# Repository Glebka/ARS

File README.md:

# ARS - Alarm System

My first project based on the STM32 microcontroller family. It consists of an alarm module and a receiver. The alarm module utilizes the RCWL-0516 motion sensor, the STM32F030K6T6 microcontroller, which wakes up upon interruption from the sensor, and communicates the alarm using the LoRa module RA-02 at 433 MHz.

As the receiver, an ESP32 TTGO LoRa 433MHz development board with an OLED display is used. The receiver spends most of its time in a sleeping state to reduce power consumption. Upon receiving an alarm signal, the receiver wakes up, displays a text status on the screen, and activates an LED indicator. The LED continues to blink even in sleep mode until the user resets the alarm state. This is made possible by the ULP coprocessor.

## TODO

- Configure the alarm module to operate on battery power.
- Implement a buzzer on the receiver to provide an audible signal in case of an alarm.
- Redesign the enclosure for the receiver.
- Design an enclosure for the alarm module.
- Add encryption
- Add protection from replay attacks

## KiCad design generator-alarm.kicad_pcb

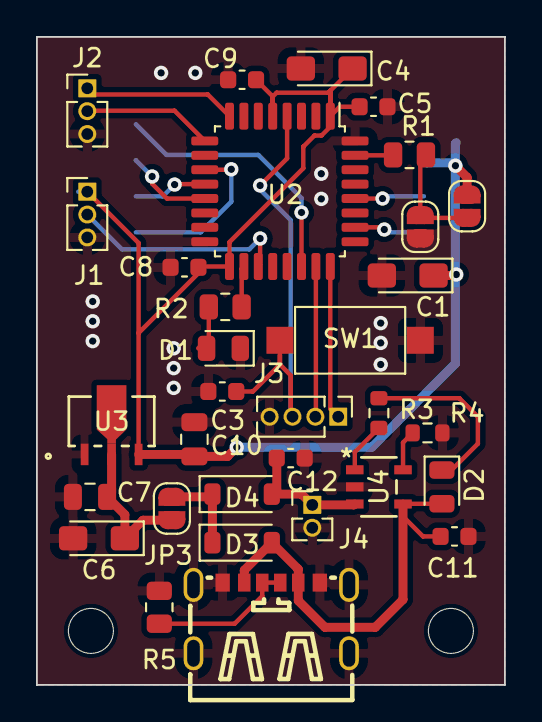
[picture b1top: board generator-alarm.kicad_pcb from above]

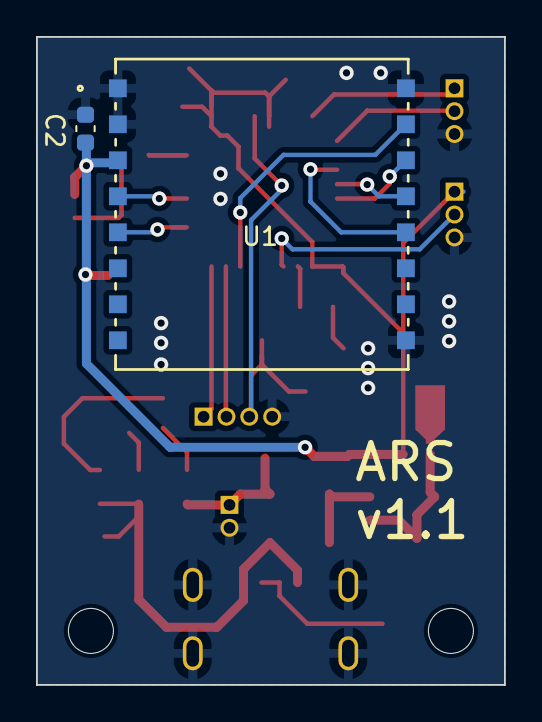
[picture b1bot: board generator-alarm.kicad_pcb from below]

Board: 2 copper layers, 26.0 x 36.0 mm, 36 parts (2 on the bottom side), 26 nets.

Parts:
C1, C4, C6: 10u; CP_EIA-3216-10_Kemet-I_Pad1.58x1.35mm_HandSolder
C2, C3, C5, C8, C9: 0.1u; C_0603_1608Metric
C7, C10: 1u; C_0805_2012Metric
C11: 1u; C_0603_1608Metric
C12: 10u; C_0603_1608Metric
D1: LED; LED_0805_2012Metric
D2: LED-Blue; LED_0805_2012Metric
D3, D4: MBR0520LT1; D_SOD-123
H1, H2: MountingHole; MountingHole_2.5mm
J1: Sensor; PinHeader_1x03_P1.27mm_Vertical
J2: UART; PinHeader_1x03_P1.27mm_Vertical
J3: SWD; PinHeader_1x04_P1.27mm_Vertical
J4: BAT; PinHeader_1x02_P1.27mm_Vertical
JP1, JP2, JP3: SolderJumper_2_Open; SolderJumper-2_P1.3mm_Open_RoundedPad1.0x1.5mm
R1: 10k; R_0805_2012Metric
R2: 1k; R_0805_2012Metric
R3: 3k; R_0603_1608Metric
R4: 5k; R_0603_1608Metric
R5: 5.1k; R_0805_2012Metric
SW1: RESET; SW_SPST_CK_RS282G05A3
U1: RA-02; RA-02_AIT
U2: STM32F030K6Tx; LQFP-32_7x7mm_P0.8mm
U3: XC6206P332PR-G; SOT-89_TOR
U4: TP4065-4.2V-SOT25-R; SOT-23-5L_TPW
USB1: TYPE-C_6P; TYPE-C-SMD_TYPE-C-6P

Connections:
BAT+: C12.1, D4.2 (A), J4.1, U4.3 (BAT)
BAT-: C1.2, C2.1, C3.1, C4.2, C5.1, C6.2, C7.2, C8.2, C9.2, C10.2, C11.2, C12.2, D1.1 (K), J1.3, J2.3, J3.4, J4.2, JP1.1 (A), R4.2, R5.2, SW1.2, U1.1 (GND), U1.2 (GND), U1.9 (GND), U1.16 (GND), U2.16 (VSS), U2.32 (VSS), U3.1 (VSS), U4.2 (GND), USB1.7 (EH), USB1.A12 (GND), USB1.B12 (GND)
MISO: U1.13 (MISO), U2.12 (PA6)
MOSI: U1.14 (MOSI), U2.13 (PA7)
MOTION_INT: J1.2, U2.19 (PA9)
NRST: C3.2, J3.3, SW1.1, U2.4 (NRST)
unnamed: D1.2 (A), R2.2
unnamed: C11.1, D2.2 (A), D3.2 (A), U4.4 (VCC), USB1.A9 (VBUS), USB1.B9 (VBUS)
unnamed: D2.1 (K), R3.2
unnamed: D3.1 (K), D4.1 (K), JP3.2 (B)
unnamed: JP1.2 (B), JP2.2 (B), R1.1
unnamed: R1.2, U2.31 (BOOT0)
unnamed: R2.1, U2.18 (PA8)
unnamed: R3.1, U4.1 (CHRG)
unnamed: R4.1, U4.5 (PROG)
unnamed: R5.1, USB1.A5 (CC1), USB1.B5 (CC2)
RA_DIO: U1.5 (DIO0), U2.26 (PB3)
RA_NSS: U1.15 (NSS), U2.22 (PA12)
RA_RST: U1.4 (RESET), U2.28 (PB5)
SCK: U1.12 (SCK), U2.11 (PA5)
SWCLK: J3.1, U2.24 (PA14)
SWDIO: J3.2, U2.23 (PA13)
UART_RX: J2.2, U2.9 (PA3)
UART_TX: J2.1, U2.8 (PA2)
V+: C6.1, C7.1, JP3.1 (A), U3.2 (VIN)
VDD: C1.1, C2.2, C4.1, C5.2, C8.1, C9.1, C10.1, J1.1, JP2.1 (A), U1.3 (3.3V), U2.1 (VDD), U2.5 (VDDA), U2.17 (VDD), U3.3 (VOUT)

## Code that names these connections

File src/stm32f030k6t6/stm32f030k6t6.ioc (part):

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Mcu.Name=STM32F030K6Tx
Mcu.Package=LQFP32
Mcu.UserName=STM32F030K6Tx
PA0.Signal=GPIO_Output
PA1.Signal=GPIO_Output
PA10.Signal=GPIO_Output
PA11.GPIOParameters=GPIO_Speed
PA11.GPIO_Speed=GPIO_SPEED_FREQ_LOW
PA11.Signal=GPIO_Output
PA12.GPIOParameters=GPIO_Speed,PinState,GPIO_Label
PA12.GPIO_Label=RA_NSS
PA12.GPIO_Speed=GPIO_SPEED_FREQ_HIGH
PA12.PinState=GPIO_PIN_SET
PA12.Signal=GPIO_Output
PA13.Mode=Serial_Wire
PA13.Signal=SYS_SWDIO
PA14.Mode=Serial_Wire
PA14.Signal=SYS_SWCLK
PA15.Signal=GPIO_Output
PA2.Mode=Asynchronous
PA2.Signal=USART1_TX
PA3.Mode=Asynchronous
PA3.Signal=USART1_RX
PA4.Signal=GPIO_Output
PA5.Mode=Full_Duplex_Master
PA5.Signal=SPI1_SCK
PA6.Mode=Full_Duplex_Master
PA6.Signal=SPI1_MISO
PA7.Mode=Full_Duplex_Master
PA7.Signal=SPI1_MOSI
PA8.GPIOParameters=GPIO_Label
PA8.GPIO_Label=STATUS_LED
PA8.Signal=GPIO_Output
PA9.GPIOParameters=GPIO_Label
PA9.GPIO_Label=MOTION_INT
PA9.Signal=GPXTI9
PB0.Signal=GPIO_Output
PB1.Signal=GPIO_Output
PB3.GPIOParameters=GPIO_Label
PB3.GPIO_Label=RA_DIO0
PB3.Signal=GPXTI3
PB4.Signal=GPIO_Output
PB5.GPIOParameters=PinState,GPIO_Label
PB5.GPIO_Label=RA_RST
PB5.PinState=GPIO_PIN_SET
PB5.Signal=GPIO_Output
PB6.Signal=GPIO_Output
PB7.Signal=GPIO_Output
PF0-OSC_IN.Signal=GPIO_Output
PF1-OSC_OUT.Signal=GPIO_Output
board=custom

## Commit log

2023-12-16 Add USB-C connector and Li-Ion charger controller
